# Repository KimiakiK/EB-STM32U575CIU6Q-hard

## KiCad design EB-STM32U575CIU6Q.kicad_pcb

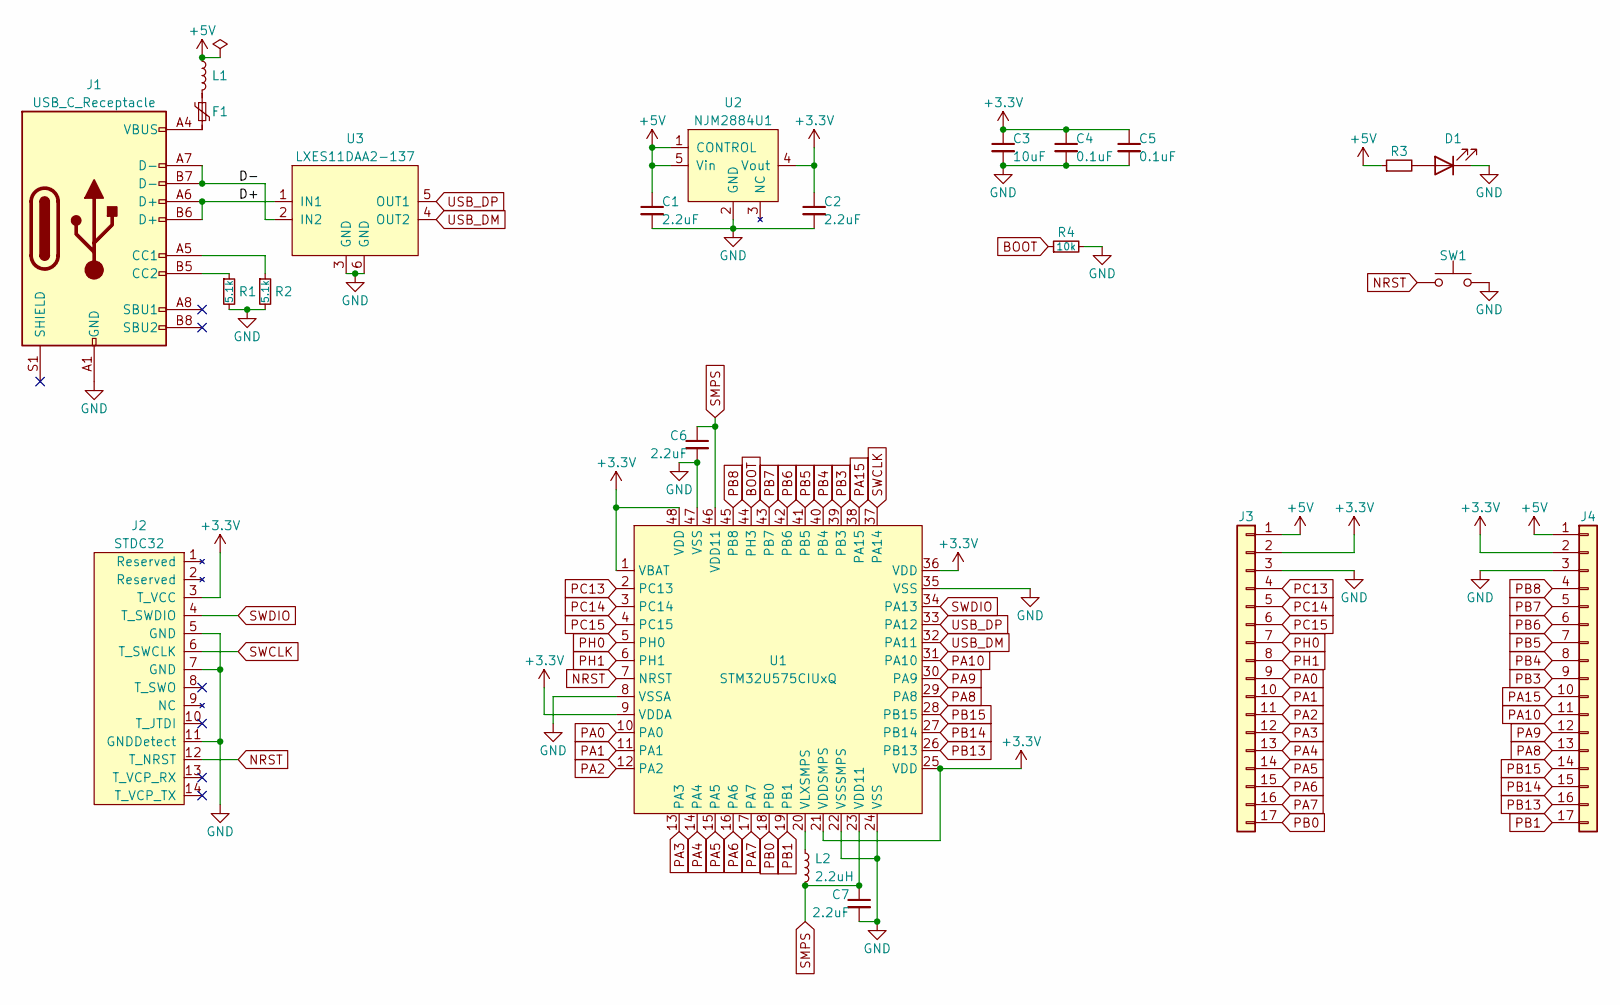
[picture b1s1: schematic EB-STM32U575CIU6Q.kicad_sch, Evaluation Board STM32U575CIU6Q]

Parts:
C1, C2, C6, C7: 2.2uF; 1005Metric
C3: 10uF; 1005Metric
C4, C5: 0.1uF; 1005Metric
D1: LED; 1608Metric
F1: Polyfuse; 1608Metric
J1: USB_C_Receptacle; USB Type-C 5077CR-16SMC2-BK-TR
J2: STDC32; BoxHeader_SMD_1.27mm_2x7pin
J3, J4: Conn_01x17; PinHeader_17pin
L1: L; 1608Metric
L2: 2.2uH; 2012Metric
R1, R2: 5.1k; 1005Metric
R3: R; 1608Metric
R4: 10k; 1005Metric
SW1: SW_Push; SW_TVAF06
U1: STM32U575CIUxQ; QFN-48-1EP_7x7mm_P0.5mm_EP5.3x5.3mm
U2: NJM2884U1; SOT-89-5
U3: LXES11DAA2-137; LXES11D

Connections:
+3.3V: C2.1, C3.1, C4.1, C5.1, J2.3 (T_VCC), J3.2, J4.2, U1.1 (VBAT), U1.9 (VDDA), U1.21 (VDDSMPS), U1.25 (VDD), U1.36 (VDD), U1.48 (VDD), U2.4 (Vout)
+5V: C1.1, J3.1, J4.1, L1.1, R3.1, U2.1 (CONTROL), U2.5 (Vin)
/D+: J1.A6 (D+), J1.B6 (D+), U3.1 (IN1)
/D-: J1.A7 (D-), J1.B7 (D-), U3.2 (IN2)
BOOT: R4.1, U1.44 (PH3)
GND: C1.2, C2.2, C3.2, C4.2, C5.2, C6.2, C7.2, D1.1 (K), J1.A1 (GND), J1.A12 (GND), J1.B1 (GND), J1.B12 (GND), J2.5 (GND), J2.7 (GND), J2.11 (GNDDetect), J3.3, J4.3, R1.2, R2.2, R4.2, SW1.2, U1.8 (VSSA), U1.22 (VSSSMPS), U1.24 (VSS), U1.35 (VSS), U1.47 (VSS), U2.2 (GND), U3.3 (GND), U3.6 (GND)
NRST: J2.12 (T_NRST), SW1.1, U1.7 (NRST)
unnamed: D1.2 (A), R3.2
unnamed: F1.1, L1.2
unnamed: F1.2, J1.A4 (VBUS), J1.A9 (VBUS), J1.B4 (VBUS), J1.B9 (VBUS)
unnamed: J1.A5 (CC1), R2.1
unnamed: J1.B5 (CC2), R1.1
unnamed: L2.1, U1.20 (VLXSMPS)
PA0: J3.9, U1.10 (PA0)
PA1: J3.10, U1.11 (PA1)
PA2: J3.11, U1.12 (PA2)
PA3: J3.12, U1.13 (PA3)
PA4: J3.13, U1.14 (PA4)
PA5: J3.14, U1.15 (PA5)
PA6: J3.15, U1.16 (PA6)
PA7: J3.16, U1.17 (PA7)
PA8: J4.13, U1.29 (PA8)
PA9: J4.12, U1.30 (PA9)
PA10: J4.11, U1.31 (PA10)
PA15: J4.10, U1.38 (PA15)
PB0: J3.17, U1.18 (PB0)
PB1: J4.17, U1.19 (PB1)
PB3: J4.9, U1.39 (PB3)
PB4: J4.8, U1.40 (PB4)
PB5: J4.7, U1.41 (PB5)
PB6: J4.6, U1.42 (PB6)
PB7: J4.5, U1.43 (PB7)
PB8: J4.4, U1.45 (PB8)
PB13: J4.16, U1.26 (PB13)
PB14: J4.15, U1.27 (PB14)
PB15: J4.14, U1.28 (PB15)
PC13: J3.4, U1.2 (PC13)
PC14: J3.5, U1.3 (PC14)
PC15: J3.6, U1.4 (PC15)
PH0: J3.7, U1.5 (PH0)
PH1: J3.8, U1.6 (PH1)
SMPS: C6.1, C7.1, L2.2, U1.23 (VDD11), U1.46 (VDD11)
SWCLK: J2.6 (T_SWCLK), U1.37 (PA14)
SWDIO: J2.4 (T_SWDIO), U1.34 (PA13)
USB_DM: U1.32 (PA11), U3.4 (OUT2)
USB_DP: U1.33 (PA12), U3.5 (OUT1)

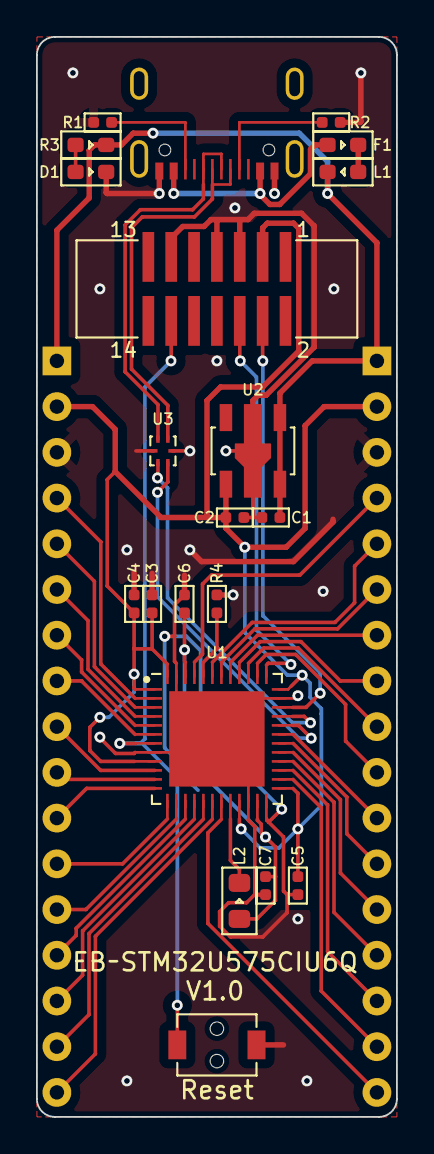
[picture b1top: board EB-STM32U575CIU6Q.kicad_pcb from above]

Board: 2 copper layers, 20.0 x 60.0 mm, 23 parts (0 on the bottom side), 46 nets.

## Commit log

2023-03-20 基板V1.0
